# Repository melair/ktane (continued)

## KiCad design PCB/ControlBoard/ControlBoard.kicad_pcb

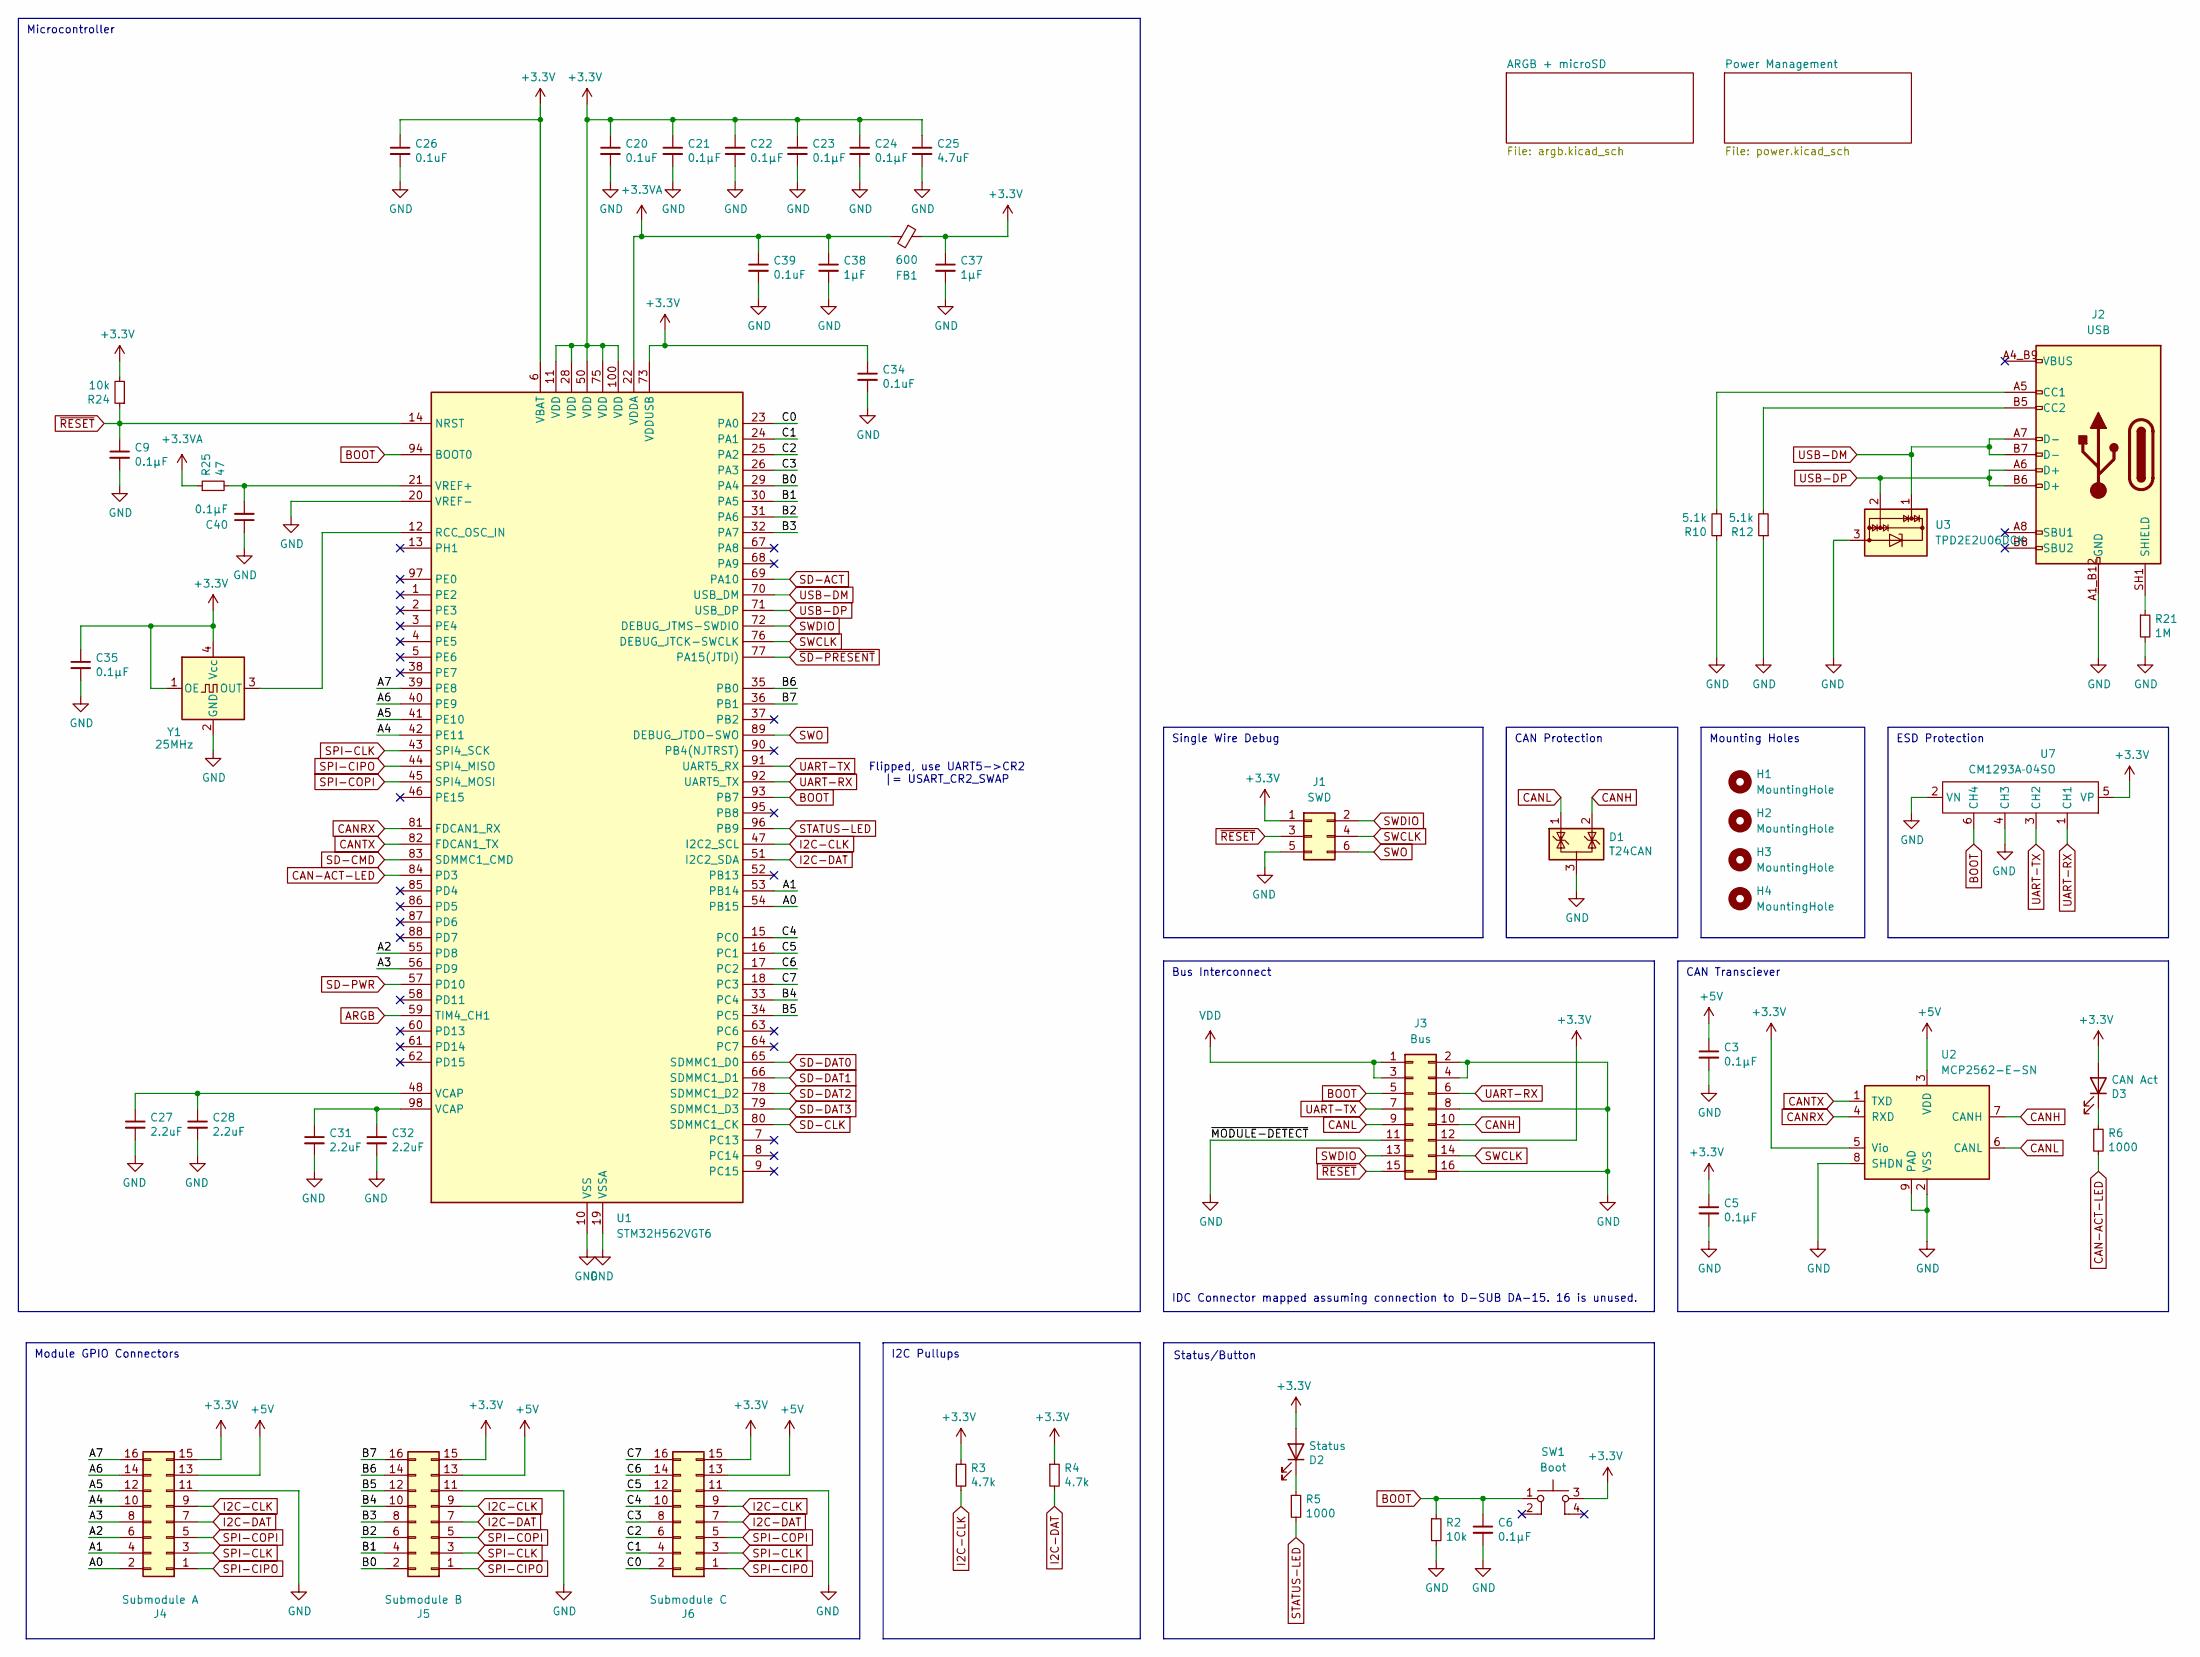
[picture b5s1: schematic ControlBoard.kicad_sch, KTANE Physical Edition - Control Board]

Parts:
C3, C5, C6, C9, C21, C22, C23, C24, C35, C40: 0.1μF; C_0603_1608Metric; DIGIKEY 1276-1005-1-ND
C20, C26, C34, C39: 0.1uF; C_0603_1608Metric; DIGIKEY 1276-1005-1-ND
C25: 4.7uF; C_0603_1608Metric; DIGIKEY 1276-2087-1-ND
C27, C28, C31, C32: 2.2uF; C_0603_1608Metric; DIGIKEY 1276-2018-1-ND
C37, C38: 1μF; C_0603_1608Metric; DIGIKEY 1276-1024-1-ND
D1: T24CAN; SOT-23; DIGIKEY CDSOT23-T24CANCT-ND
D2: Status; LED_0603_1608Metric; DIGIKEY 3147-B19Y1UYG-20C000313U1930CT-ND
D3: CAN Act; LED_0603_1608Metric; DIGIKEY 3147-B19Y1UYG-20C000313U1930CT-ND
FB1: 600; L_0603_1608Metric; DIGIKEY 490-1014-1-ND
H1, H2, H3, H4: MountingHole; MountingHole_3.2mm_M3_NoCopper
J1: SWD; Tag-Connect_TC2030-IDC-NL_2x03_P1.27mm_Vertical
J2: USB; SAMESKY_UJ20-C-H-G-SMT-1A-P16-TR; DIGIKEY 2223-UJ20-C-H-G-SMT-1A-P16-TRCT-ND
J3: Bus; PinHeader_2x08_P2.54mm_VerticalAndHorizontal_Centered; DIGIKEY STOCK/HEADER
J4: Submodule A; PinHeader_2x08_P2.54mm_Vertical-Centered; DIGIKEY S9171-ND
J5: Submodule B; PinHeader_2x08_P2.54mm_Vertical-Centered; DIGIKEY S9171-ND
J6: Submodule C; PinHeader_2x08_P2.54mm_Vertical-Centered; DIGIKEY S9171-ND
R2, R24: 10k; R_0603_1608Metric; DIGIKEY P10.0KHCT-ND
R3, R4: 4.7k; R_0603_1608Metric; DIGIKEY P4.70KHCT-ND
R5, R6: 1000; R_0603_1608Metric; DIGIKEY P1.00KHCT-ND
R10, R12: 5.1k; R_0603_1608Metric; DIGIKEY P5.10KHCT-ND
R21: 1M; R_0603_1608Metric; DIGIKEY P1.00MHCT-ND
R25: 47; R_0603_1608Metric; DIGIKEY 541-47.0HCT-ND
SW1: Boot; PTS526Sx15SMTR2xLFS; DIGIKEY CKN12220-1-ND
U1: STM32H562VGT6; LQFP-100_14x14mm_P0.5mm; DIGIKEY 497-STM32H562VGT6-ND
U2: MCP2562-E-SN; DFN-8-1EP_3x3mm_P0.65mm_EP1.55x2.4mm; DIGIKEY MCP2562T-E/MFCT-ND
U3: TPD2E2U06DCK; SOT-323_SC-70; DIGIKEY TPD2E2U06DCKR
U7: CM1293A‐04SO; SC-74-6_1.55x2.9mm_P0.95mm; DIGIKEY CM1293A-04SOOSCT-ND
Y1: 25MHz; Oscillator_SMD-Vishay_X022C_2.5mmx2.0mm; DIGIKEY 541-XO22C3EREHX25M000CT-ND

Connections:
+3.3V: C5.1, C20.1, C21.1, C22.1, C23.1, C24.1, C25.1, C26.1, C34.1, C35.1, C37.1, D2.2 (A), D3.2 (A), FB1.1, J1.1, J3.12, J4.15, J5.15, J6.15, R3.1, R4.1, R24.2, SW1.3, U1.6 (VBAT), U1.11 (VDD), U1.28 (VDD), U1.50 (VDD), U1.73 (VDDUSB), U1.75 (VDD), U1.100 (VDD), U2.5 (Vio), U7.5 (VP), Y1.1 (OE), Y1.4 (Vcc); also elsewhere on the board
+3.3VA: C38.1, C39.1, FB1.2, R25.1, U1.22 (VDDA)
+5V: C3.1, J4.13, J5.13, J6.13, U2.3 (VDD); also elsewhere on the board
/A0: J4.2, U1.54 (PB15)
/A1: J4.4, U1.53 (PB14)
/A2: J4.6, U1.55 (PD8)
/A3: J4.8, U1.56 (PD9)
/A4: J4.10, U1.42 (PE11)
/A5: J4.12, U1.41 (PE10)
/A6: J4.14, U1.40 (PE9)
/A7: J4.16, U1.39 (PE8)
/B0: J5.2, U1.29 (PA4)
/B1: J5.4, U1.30 (PA5)
/B2: J5.6, U1.31 (PA6)
/B3: J5.8, U1.32 (PA7)
/B4: J5.10, U1.33 (PC4)
/B5: J5.12, U1.34 (PC5)
/B6: J5.14, U1.35 (PB0)
/B7: J5.16, U1.36 (PB1)
/C0: J6.2, U1.23 (PA0)
/C1: J6.4, U1.24 (PA1)
/C2: J6.6, U1.25 (PA2)
/C3: J6.8, U1.26 (PA3)
/C4: J6.10, U1.15 (PC0)
/C5: J6.12, U1.16 (PC1)
/C6: J6.14, U1.17 (PC2)
/C7: J6.16, U1.18 (PC3)
ARGB: U1.59 (TIM4_CH1); also elsewhere on the board
BOOT: C6.1, J3.5, R2.1, SW1.1, U1.93 (PB7), U1.94 (BOOT0), U7.6 (CH4)
CAN-ACT-LED: R6.2, U1.84 (PD3)
CANH: D1.2 (K), J3.10, U2.7 (CANH)
CANL: D1.1 (K), J3.9, U2.6 (CANL)
CANRX: U1.81 (FDCAN1_RX), U2.4 (RXD)
CANTX: U1.82 (FDCAN1_TX), U2.1 (TXD)
GND: C3.2, C5.2, C6.2, C9.2, C20.2, C21.2, C22.2, C23.2, C24.2, C25.2, C26.2, C27.2, C28.2, C31.2, C32.2, C34.2, C35.2, C37.2, C38.2, C39.2, C40.1, D1.3 (A), J1.5, J2.A1_B12 (GND), J2.B1_A12 (GND), J3.2, J3.4, J3.8, J3.11, J3.16, J4.11, J5.11, J6.11, R2.2, R10.1, R12.1, R21.2, U1.10 (VSS), U1.19 (VSSA), U1.20 (VREF-), U1.27 (VSS), U1.49 (VSS), U1.74 (VSS), U1.99 (VSS), U2.2 (VSS), U2.8 (SHDN), U2.9 (PAD), U3.3, U7.2 (VN), U7.4 (CH3), Y1.2 (GND); also elsewhere on the board
I2C-CLK: J4.9, J5.9, J6.9, R3.2, U1.47 (I2C2_SCL)
I2C-DAT: J4.7, J5.7, J6.7, R4.2, U1.51 (I2C2_SDA)
unnamed: C27.1, C28.1, U1.48 (VCAP)
unnamed: C31.1, C32.1, U1.98 (VCAP)
unnamed: D2.1 (K), R5.1
unnamed: D3.1 (K), R6.1
unnamed: J2.A5 (CC1), R10.2
unnamed: J2.B5 (CC2), R12.2
unnamed: U1.12 (RCC_OSC_IN), Y1.3 (OUT)
unnamed: C40.2, R25.2, U1.21 (VREF+)
SD-ACT: U1.69 (PA10); also elsewhere on the board
SD-CLK: U1.80 (SDMMC1_CK); also elsewhere on the board
SD-CMD: U1.83 (SDMMC1_CMD); also elsewhere on the board
SD-DAT0: U1.65 (SDMMC1_D0); also elsewhere on the board
SD-DAT1: U1.66 (SDMMC1_D1); also elsewhere on the board
SD-DAT2: U1.78 (SDMMC1_D2); also elsewhere on the board
SD-DAT3: U1.79 (SDMMC1_D3); also elsewhere on the board
SD-PWR: U1.57 (PD10); also elsewhere on the board
SPI-CIPO: J4.1, J5.1, J6.1, U1.44 (SPI4_MISO)
SPI-CLK: J4.3, J5.3, J6.3, U1.43 (SPI4_SCK)
SPI-COPI: J4.5, J5.5, J6.5, U1.45 (SPI4_MOSI)
STATUS-LED: R5.2, U1.96 (PB9)
SWCLK: J1.4, J3.14, U1.76 (DEBUG_JTCK-SWCLK)
SWDIO: J1.2, J3.13, U1.72 (DEBUG_JTMS-SWDIO)
SWO: J1.6, U1.89 (DEBUG_JTDO-SWO)
UART-RX: J3.6, U1.92 (UART5_TX), U7.1 (CH1)
UART-TX: J3.7, U1.91 (UART5_RX), U7.3 (CH2)
USB-DM: J2.A7 (D-), J2.B7 (D-), U1.70 (USB_DM), U3.1
USB-DP: J2.A6 (D+), J2.B6 (D+), U1.71 (USB_DP), U3.2
VDD: J3.1, J3.3; also elsewhere on the board
~RESET: C9.1, J1.3, J3.15, R24.1, U1.14 (NRST)
~SD-PRESENT: U1.77 (PA15(JTDI)); also elsewhere on the board

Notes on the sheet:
Status/Button
Bus Interconnect
Single Wire Debug
Module GPIO Connectors
Microcontroller
CAN Protection
Flipped, use UART5->CR2 |= USART_CR2_SWAP
IDC Connector mapped assuming connection to D-SUB DA-15. 16 is unused.
Mounting Holes
ESD Protection
CAN Transciever
I2C Pullups

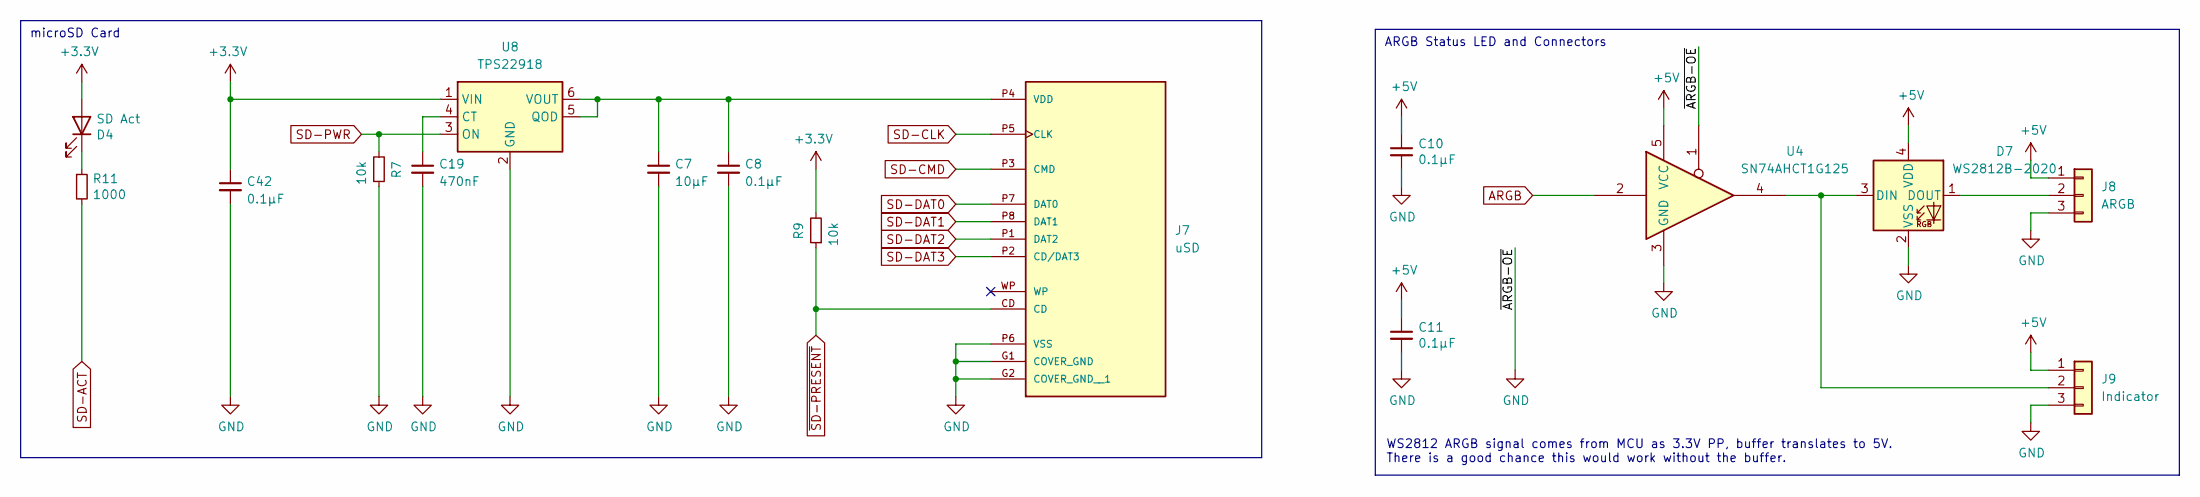
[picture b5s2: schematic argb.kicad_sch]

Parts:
C7: 10μF; C_0603_1608Metric; DIGIKEY 1276-1948-1-ND
C8, C10, C11, C42: 0.1μF; C_0603_1608Metric; DIGIKEY 1276-1005-1-ND
C19: 470nF; C_0603_1608Metric; DIGIKEY 1276-1094-1-ND
D4: SD Act; LED_0603_1608Metric; DIGIKEY 3147-B19Y1UYG-20C000313U1930CT-ND
D7: WS2812B-2020; LED_WS2812B-2020_PLCC4_2.0x2.0mm; DIGIKEY STOCK/ALIEXPRESS
J7: uSD; CUI_MSD-11-A; PARTREV 1.02; DIGIKEY 2223-MSD-11-ACT-ND
J8: ARGB; JST_PH_B3B-PH-SM4-TB_1x03-1MP_P2.00mm_Vertical; DIGIKEY 455-B3B-PH-SM4-TBCT-ND
J9: Indicator; JST_PH_B3B-PH-SM4-TB_1x03-1MP_P2.00mm_Vertical; DIGIKEY 455-B3B-PH-SM4-TBCT-ND
R7, R9: 10k; R_0603_1608Metric; DIGIKEY P10.0KHCT-ND
R11: 1000; R_0603_1608Metric; DIGIKEY P1.00KHCT-ND
U4: SN74AHCT1G125; SOT-23-5; DIGIKEY 296-4708-1-ND
U8: TPS22918; SOT-23-6; DIGIKEY 296-44632-1-ND

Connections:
+3.3V: C42.1, D4.2 (A), R9.2, U8.1 (VIN); also elsewhere on the board
+5V: C10.1, C11.1, D7.4 (VDD), J8.1, J9.1, U4.5 (VCC); also elsewhere on the board
ARGB: U4.2; also elsewhere on the board
GND: C7.2, C8.2, C10.2, C11.2, C19.2, C42.2, D7.2 (VSS), J7.G1 (COVER_GND), J7.G2 (COVER_GND__1), J7.P6 (VSS), J8.3, J9.3, R7.1, U4.1, U4.3 (GND), U8.2 (GND); also elsewhere on the board
unnamed: D4.1 (K), R11.1
unnamed: D7.3 (DIN), J9.2, U4.4
unnamed: D7.1 (DOUT), J8.2
unnamed: C7.1, C8.1, J7.P4 (VDD), U8.5 (QOD), U8.6 (VOUT)
unnamed: C19.1, U8.4 (CT)
SD-ACT: R11.2; also elsewhere on the board
SD-CLK: J7.P5 (CLK); also elsewhere on the board
SD-CMD: J7.P3 (CMD); also elsewhere on the board
SD-DAT0: J7.P7 (DAT0); also elsewhere on the board
SD-DAT1: J7.P8 (DAT1); also elsewhere on the board
SD-DAT2: J7.P1 (DAT2); also elsewhere on the board
SD-DAT3: J7.P2 (CD/DAT3); also elsewhere on the board
SD-PWR: R7.2, U8.3 (ON); also elsewhere on the board
~SD-PRESENT: J7.CD, R9.1; also elsewhere on the board

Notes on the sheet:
microSD Card
WS2812 ARGB signal comes from MCU as 3.3V PP, buffer translates to 5V. There is a good chance this would work without the buffer.
ARGB Status LED and Connectors

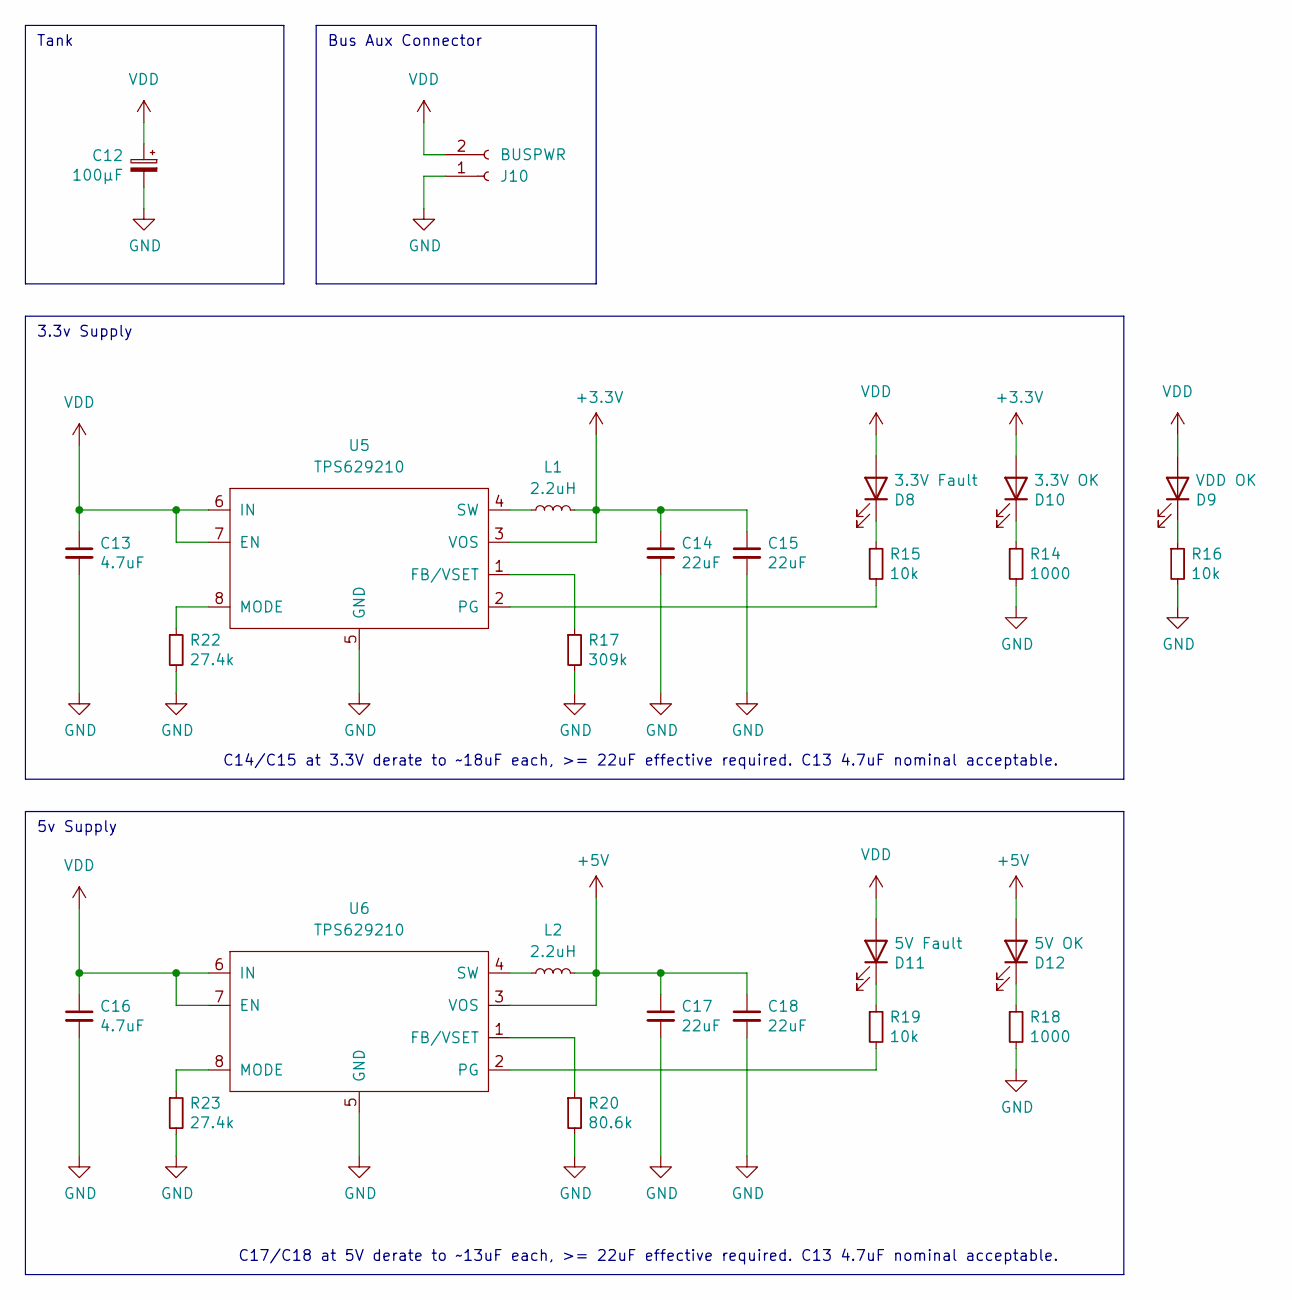
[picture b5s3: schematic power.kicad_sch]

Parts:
C12: 100μF; C_Elec_6.3x7.7; DIGIKEY 399-A768EB107M1ELAE036CT-ND
C13, C16: 4.7uF; C_1206_3216Metric; DIGIKEY 445-1606-1-ND
C14, C15, C17, C18: 22uF; C_1206_3216Metric; DIGIKEY 1276-3148-1-ND
D8: 3.3V Fault; LED_0603_1608Metric; DIGIKEY 3147-B19Y1USD-20C000113U1930CT-ND
D9: VDD OK; LED_0603_1608Metric; DIGIKEY 3147-B19Y1USD-20C000113U1930CT-ND
D10: 3.3V OK; LED_0603_1608Metric; DIGIKEY 3147-B19Y1UYG-20C000313U1930CT-ND
D11: 5V Fault; LED_0603_1608Metric; DIGIKEY 3147-B19Y1USD-20C000113U1930CT-ND
D12: 5V OK; LED_0603_1608Metric; DIGIKEY 3147-B19Y1UYG-20C000313U1930CT-ND
J10: BUSPWR; AMASS_XT30PW-F_1x02_P2.50mm_Horizontal; DIGIKEY STOCK/AMASS
L1, L2: 2.2uH; L_1008_2520Metric; DIGIKEY 490-DFE252012PD-2R2M=P2CT-ND
R14, R18: 1000; R_0603_1608Metric; DIGIKEY P1.00KHCT-ND
R15, R16, R19: 10k; R_0603_1608Metric; DIGIKEY P10.0KHCT-ND
R17: 309k; R_0603_1608Metric; DIGIKEY P309KHCT-ND
R20: 80.6k; R_0603_1608Metric; DIGIKEY P80.6KHCT-ND
R22, R23: 27.4k; R_0603_1608Metric; DIGIKEY P27.4KHCT-ND
U5, U6: TPS629210; SOT-583-8; DIGIKEY 296-TPS629210DRLRCT-ND

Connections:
+3.3V: C14.1, C15.1, D10.2 (A), L1.2, U5.3 (VOS); also elsewhere on the board
+5V: C17.1, C18.1, D12.2 (A), L2.2, U6.3 (VOS); also elsewhere on the board
GND: C12.2, C13.2, C14.2, C15.2, C16.2, C17.2, C18.2, J10.1, R14.2, R16.2, R17.2, R18.2, R20.2, R22.2, R23.2, U5.5 (GND), U6.5 (GND); also elsewhere on the board
unnamed: D8.1 (K), R15.1
unnamed: D9.1 (K), R16.1
unnamed: D10.1 (K), R14.1
unnamed: D11.1 (K), R19.1
unnamed: D12.1 (K), R18.1
unnamed: R17.1, U5.1 (FB/VSET)
unnamed: R22.1, U5.8 (MODE)
unnamed: R15.2, U5.2 (PG)
unnamed: L1.1, U5.4 (SW)
unnamed: R20.1, U6.1 (FB/VSET)
unnamed: R23.1, U6.8 (MODE)
unnamed: R19.2, U6.2 (PG)
unnamed: L2.1, U6.4 (SW)
VDD: C12.1, C13.1, C16.1, D8.2 (A), D9.2 (A), D11.2 (A), J10.2, U5.6 (IN), U5.7 (EN), U6.6 (IN), U6.7 (EN); also elsewhere on the board

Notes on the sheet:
3.3v Supply
C17/C18 at 5V derate to ~13uF each, >= 22uF effective required. C13 4.7uF nominal acceptable.
Bus Aux Connector
5v Supply
Tank
C14/C15 at 3.3V derate to ~18uF each, >= 22uF effective required. C13 4.7uF nominal acceptable.

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
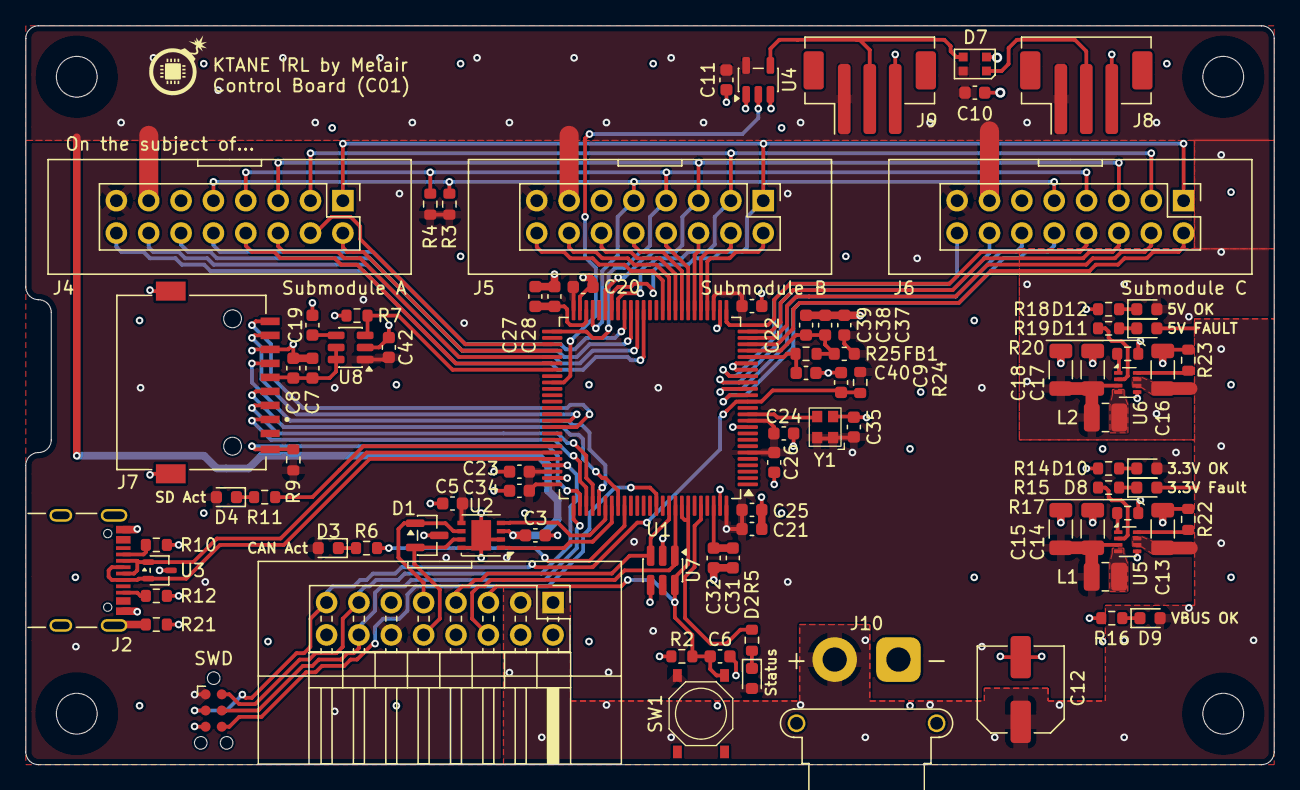
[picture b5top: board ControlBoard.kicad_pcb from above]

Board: 4 copper layers, 98.0 x 58.0 mm, 93 parts (0 on the bottom side), 86 nets.

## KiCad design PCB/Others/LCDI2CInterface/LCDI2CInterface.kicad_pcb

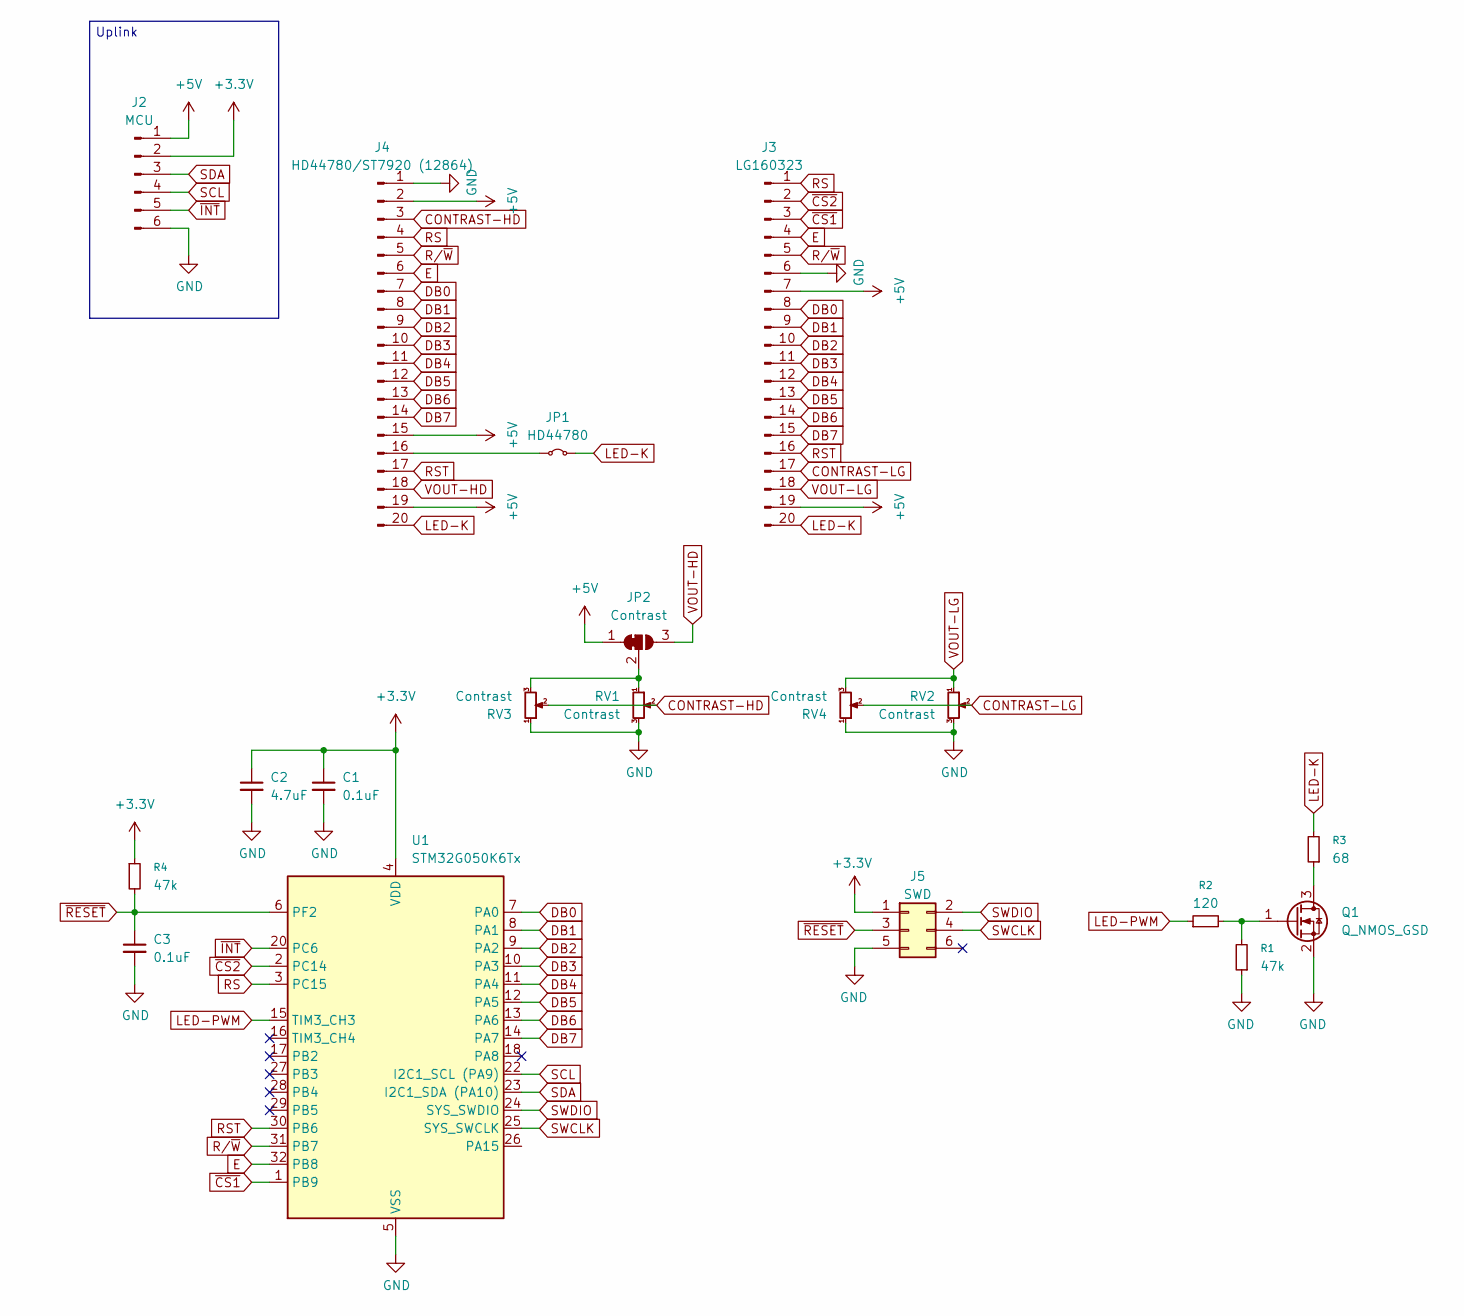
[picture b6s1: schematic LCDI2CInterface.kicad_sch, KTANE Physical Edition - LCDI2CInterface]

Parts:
C1, C3: 0.1uF; C_0603_1608Metric
C2: 4.7uF; C_0603_1608Metric
J2: MCU; PinHeader_1x06_P2.54mm_Horizontal
J3: LG160323; PinHeader_1x20_P2.54mm_Vertical
J4: HD44780/ST7920 (12864); PinHeader_1x20_P2.54mm_Vertical
J5: SWD; Tag-Connect_TC2030-IDC-NL_2x03_P1.27mm_Vertical; DIGIKEY NONE
JP1: HD44780; SolderJumper-2_P1.3mm_Bridged_RoundedPad1.0x1.5mm
JP2: Contrast; SolderJumper-3_P1.3mm_Bridged12_RoundedPad1.0x1.5mm
Q1: Q_NMOS_GSD; SOT-23
R1, R4: 47k; R_0603_1608Metric
R2: 120; R_0603_1608Metric
R3: 68; R_0603_1608Metric
RV1, RV2, RV3, RV4: Contrast; Potentiometer_Bourns_TC33X_Vertical; DIGIKEY TC33X-103ECT-ND
U1: STM32G050K6Tx; LQFP-32_7x7mm_P0.8mm

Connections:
+3.3V: C1.1, C2.1, J2.2, J5.1, R4.1, U1.4 (VDD)
+5V: J2.1, J3.7, J3.19, J4.2, J4.15, J4.19, JP2.1 (A)
CONTRAST-HD: J4.3, RV1.2, RV3.2
CONTRAST-LG: J3.17, RV2.2, RV4.2
DB0: J3.8, J4.7, U1.7 (PA0)
DB1: J3.9, J4.8, U1.8 (PA1)
DB2: J3.10, J4.9, U1.9 (PA2)
DB3: J3.11, J4.10, U1.10 (PA3)
DB4: J3.12, J4.11, U1.11 (PA4)
DB5: J3.13, J4.12, U1.12 (PA5)
DB6: J3.14, J4.13, U1.13 (PA6)
DB7: J3.15, J4.14, U1.14 (PA7)
E: J3.4, J4.6, U1.32 (PB8)
GND: C1.2, C2.2, C3.2, J2.6, J3.6, J4.1, J5.5, Q1.2 (S), R1.1, RV1.3, RV2.3, RV3.1, RV4.1, U1.5 (VSS)
LED-K: J3.20, J4.20, JP1.2 (B), R3.2
LED-PWM: R2.1, U1.15 (TIM3_CH3)
unnamed: J4.16, JP1.1 (A)
unnamed: JP2.2 (C), RV1.1, RV3.3
unnamed: Q1.3 (D), R3.1
unnamed: Q1.1 (G), R1.2, R2.2
RS: J3.1, J4.4, U1.3 (PC15)
RST: J3.16, J4.17, U1.30 (PB6)
R/~W: J3.5, J4.5, U1.31 (PB7)
SCL: J2.4, U1.22 (I2C1_SCL (PA9))
SDA: J2.3, U1.23 (I2C1_SDA (PA10))
SWCLK: J5.4, U1.25 (SYS_SWCLK)
SWDIO: J5.2, U1.24 (SYS_SWDIO)
VOUT-HD: J4.18, JP2.3 (B)
VOUT-LG: J3.18, RV2.1, RV4.3
~CS1: J3.3, U1.1 (PB9)
~CS2: J3.2, U1.2 (PC14)
~INT: J2.5, U1.20 (PC6)
~RESET: C3.1, J5.3, R4.2, U1.6 (PF2)

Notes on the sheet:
Uplink

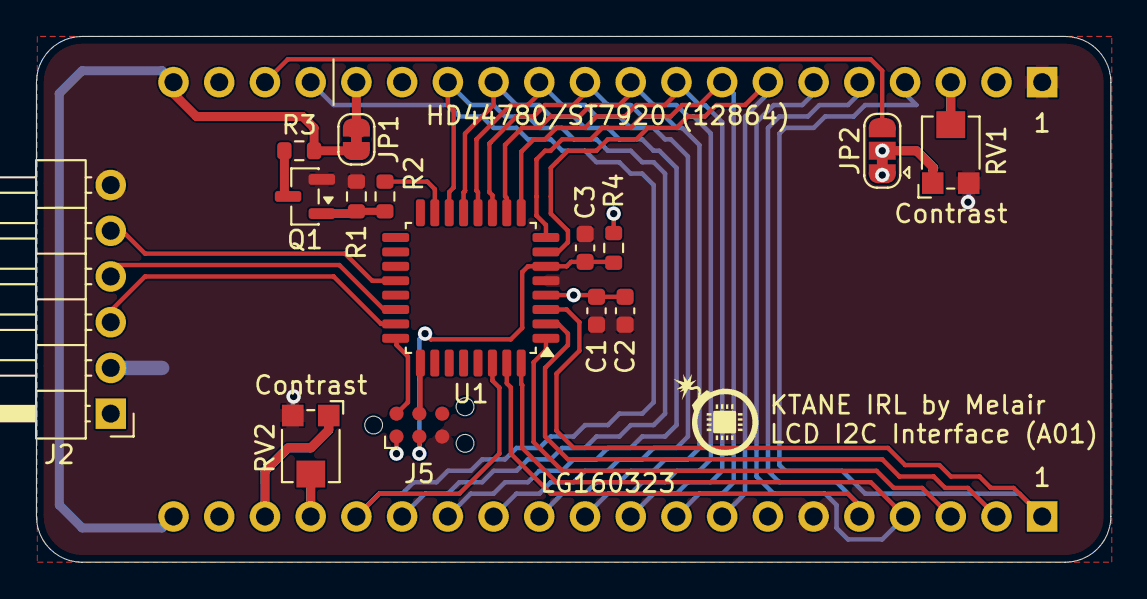
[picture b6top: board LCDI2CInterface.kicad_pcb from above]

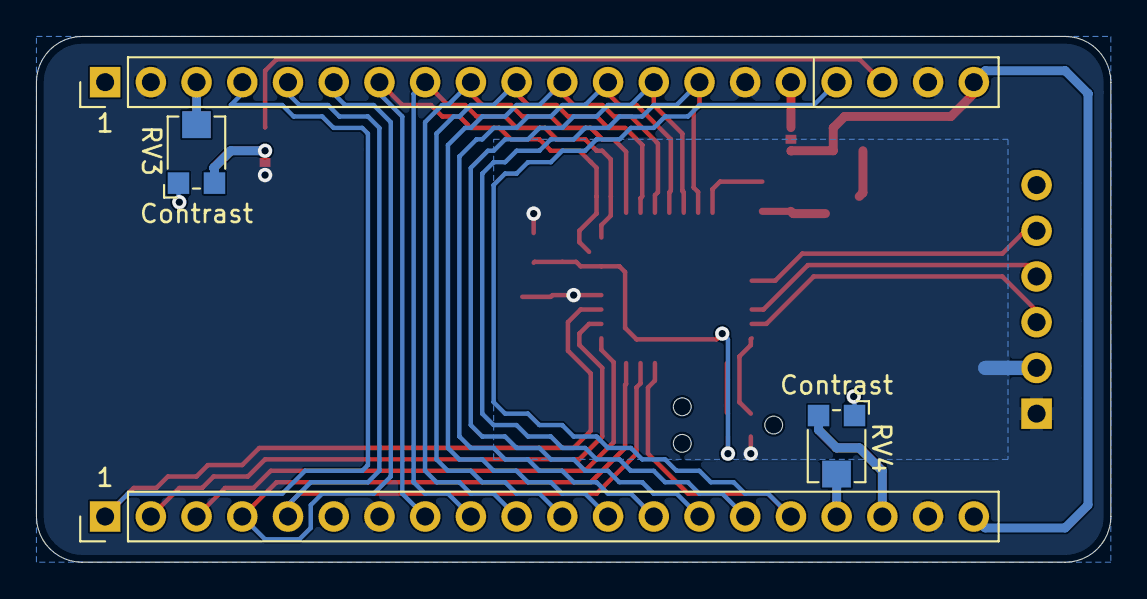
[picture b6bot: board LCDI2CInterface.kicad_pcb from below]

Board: 2 copper layers, 59.7 x 29.2 mm, 19 parts (4 on the bottom side), 33 nets.

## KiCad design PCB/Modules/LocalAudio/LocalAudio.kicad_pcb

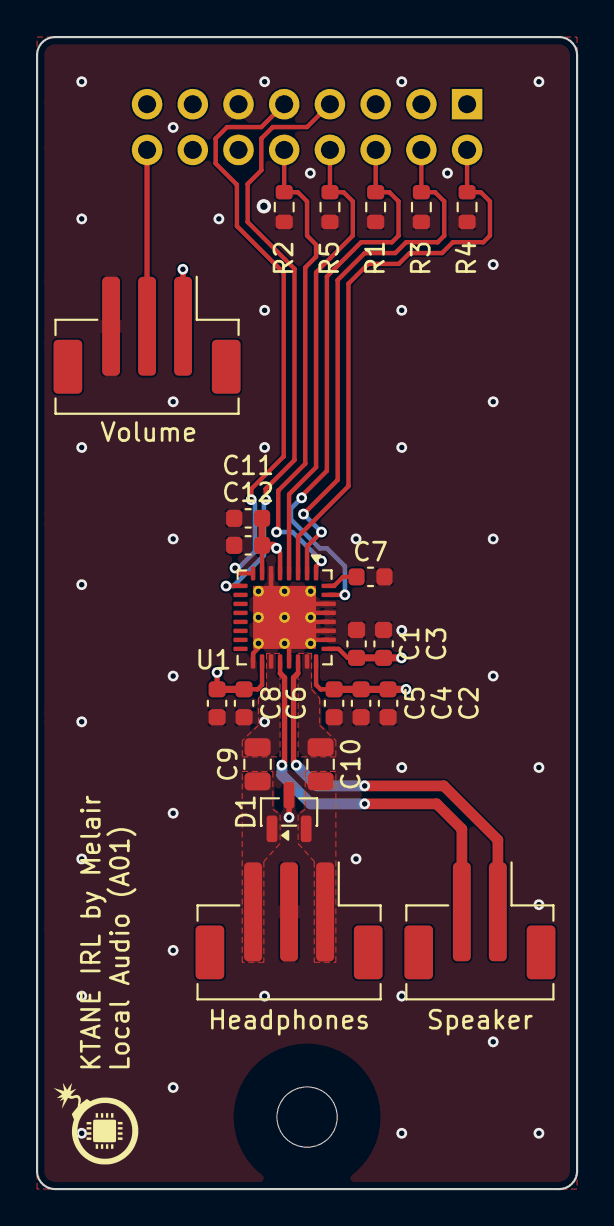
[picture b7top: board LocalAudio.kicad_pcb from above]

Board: 4 copper layers, 30.0 x 64.0 mm, 23 parts (0 on the bottom side), 17 nets.

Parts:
C1, C5, C6, C7, C12: 0.1uF; C_0603_1608Metric
C2: 10uF; C_0603_1608Metric
C3, C4, C8, C11: 1uF; C_0603_1608Metric
C9, C10: 47uF; C_0805_2012Metric
D1: PESD3V3S2BT; SOT-23
J1: In; KTANE Submodule Connector V2 - Short
J2: Speaker; JST_PH_B2B-PH-SM4-TB_1x02-1MP_P2.00mm_Vertical
J3: Headphones; JST_PH_B3B-PH-SM4-TB_1x03-1MP_P2.00mm_Vertical
J4: Volume; JST_PH_B3B-PH-SM4-TB_1x03-1MP_P2.00mm_Vertical
R1, R2, R3, R4, R5: 4.7k; R_0603_1608Metric
U1: TLV320DAC32; VQFN-32-1EP_5x5mm_P0.5mm_EP3.5x3.5mm_ThermalVias

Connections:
+3.3V: C1.2, C2.2, C3.2, C4.2, C5.2, C6.2, C8.2, C11.2, C12.2, J1.15 (3V3), J4.1, U1.5 (LDO_SELECT), U1.7 (IOVDD), U1.18 (DRVDD), U1.24 (DRVDD), U1.25 (AVDD_DAC)
GND: C1.1, C2.1, C3.1, C4.1, C5.1, C6.1, C7.1, C8.1, C11.1, C12.1, D1.3 (CC), J1.11 (GND), J3.2, J4.3, R1.1, R2.1, R3.1, R4.1, R5.1, U1.6 (IOVSS), U1.17 (DRVSS), U1.21 (DRVSS), U1.26 (VSS_DAC), U1.27 (VSS_DAC), U1.28 (VSS_DAC), U1.29 (VSS_DAC), U1.30 (VSS_DAC), U1.33 (VSS_DAC)
I2C-CLK: J1.9 (SCL), U1.8 (SCL)
I2C-DAT: J1.7 (SDA), U1.9 (SDA)
I2S-BCLK: J1.4 (I2S_CK), R3.2, U1.2 (BCLK)
I2S-DAT: J1.8 (I2S_SDO), R5.2, U1.4 (DIN)
I2S-MCLK: J1.10 (I2S_MCLK), R2.2, U1.1 (MCLK)
I2S-WCLK: J1.2 (I2S_WS), R4.2, U1.3 (WCLK)
unnamed: C9.2, D1.1 (K1), J3.3
unnamed: C10.2, D1.2 (K2), J3.1
unnamed: C7.2, U1.32 (DVDD)
unnamed: C9.1, U1.19 (HPLOUT)
unnamed: C10.1, U1.23 (HPROUT)
SPK+: J2.1, U1.22 (HPRCOM)
SPK-: J2.2, U1.20 (HPLCOM)
VOL: J1.16 (I7), J4.2
~RESET: J1.6 (I2S_SDI), R1.2, U1.31 (~RESET)
